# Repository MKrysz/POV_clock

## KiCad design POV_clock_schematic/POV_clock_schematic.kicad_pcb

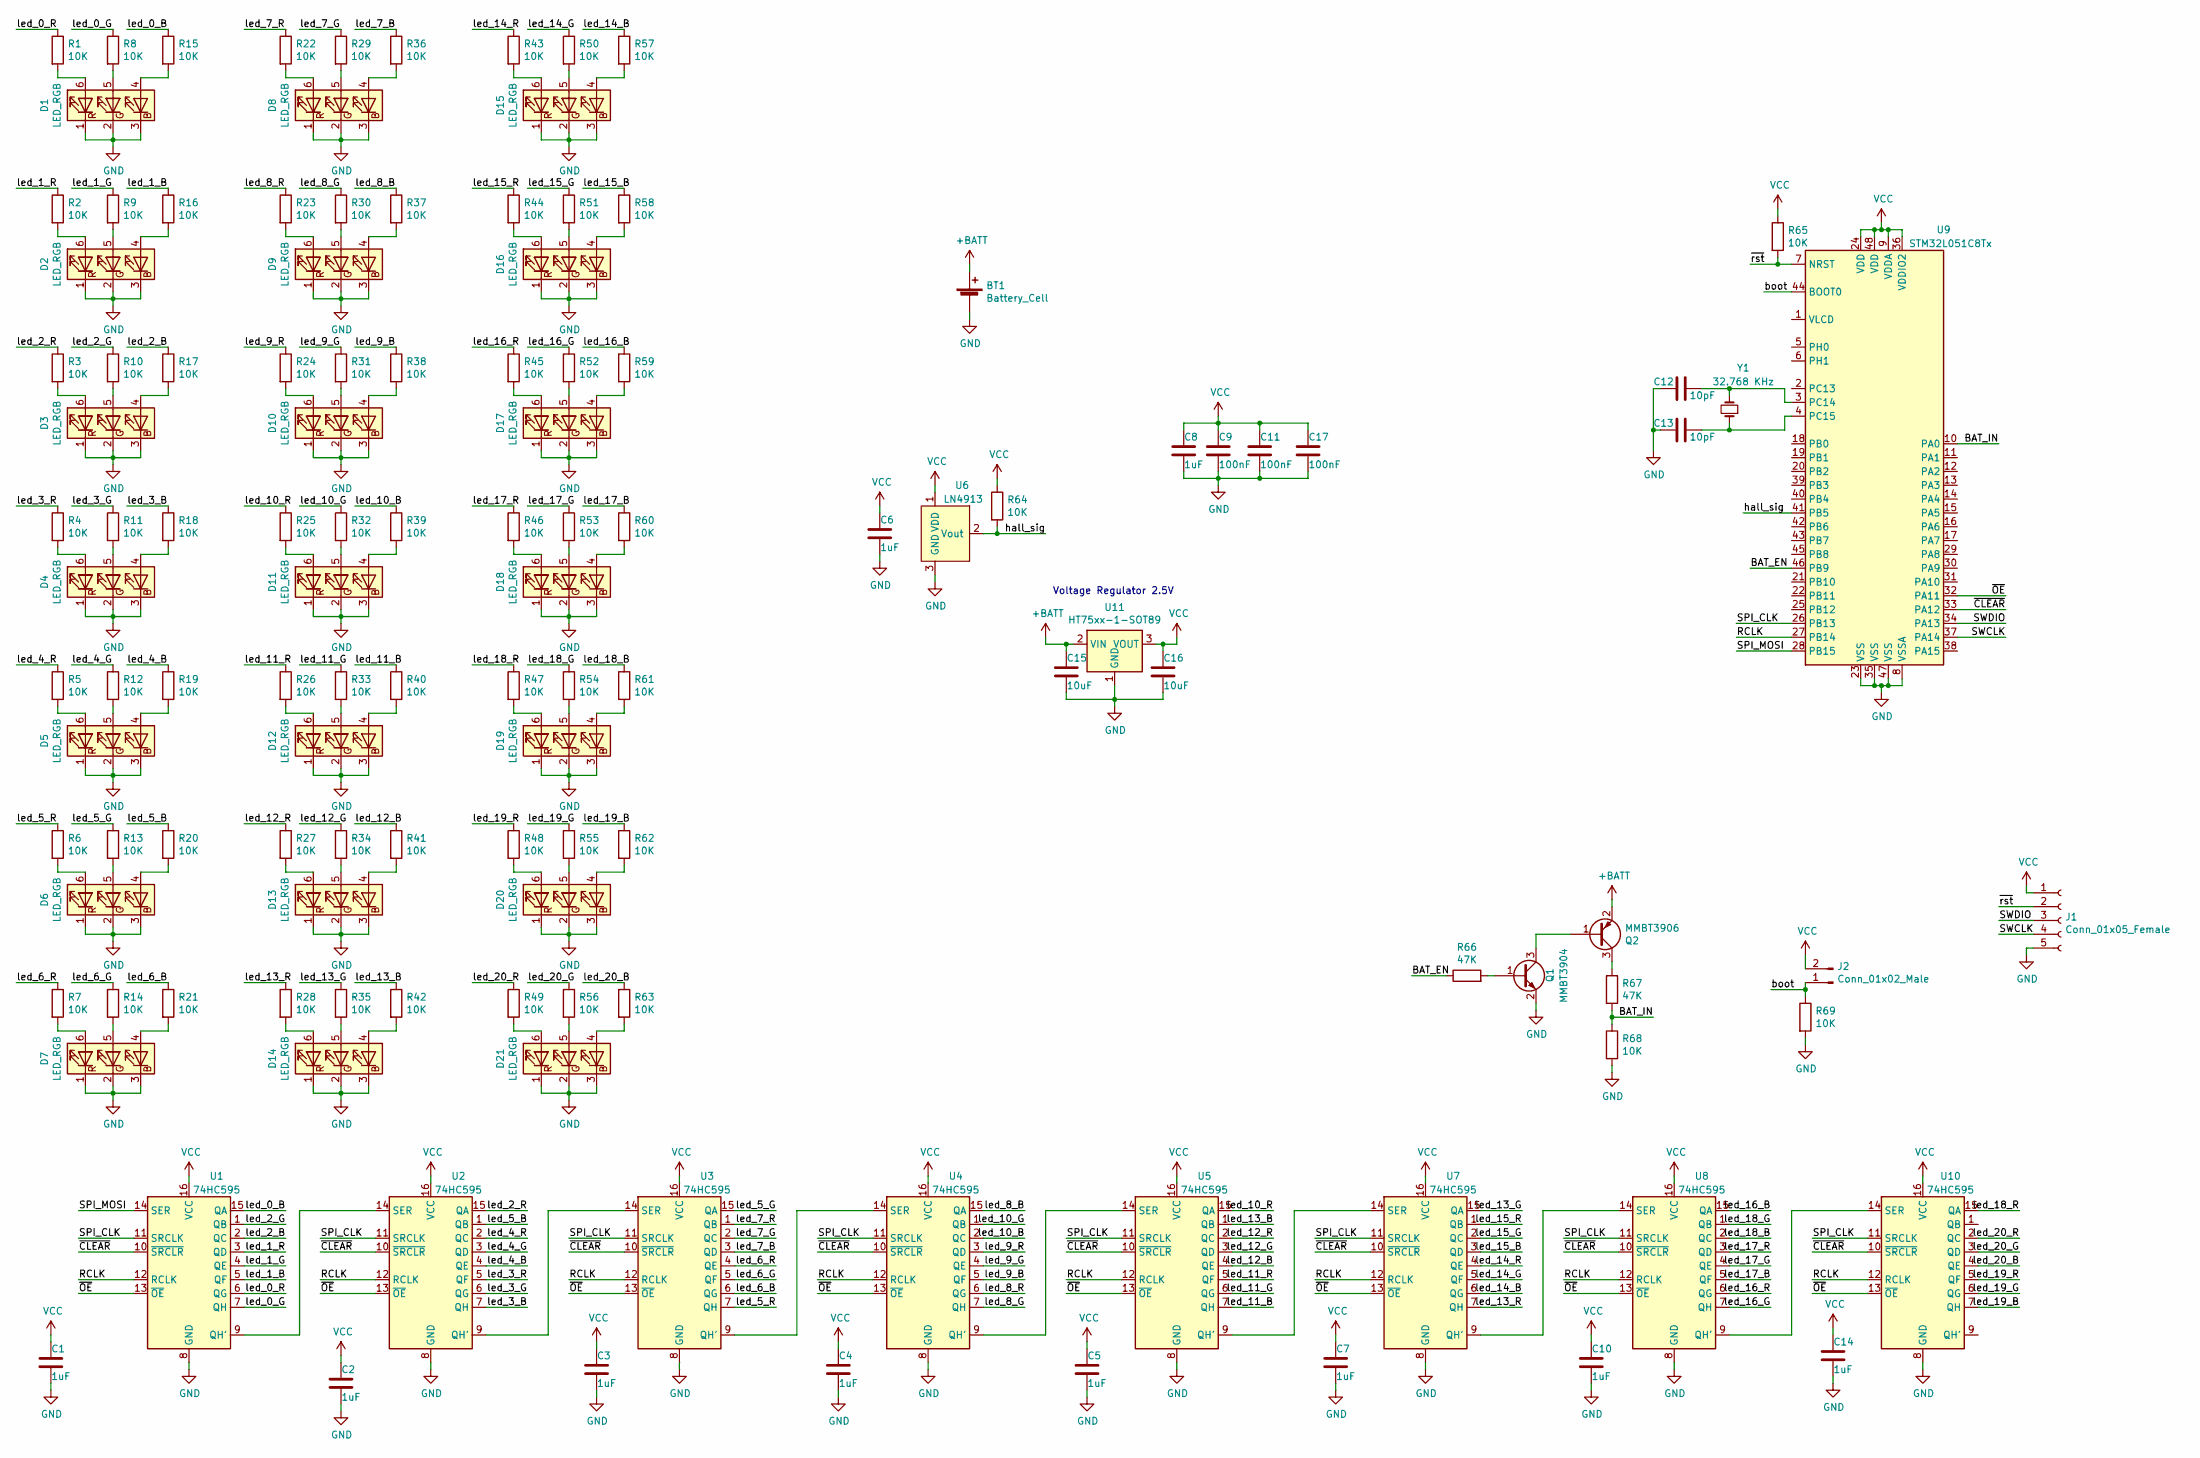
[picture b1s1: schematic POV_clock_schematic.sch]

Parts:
BT1: Battery_Cell; PinHeader_1x02_P2.54mm_Vertical
C1, C2, C3, C4, C5, C6, C7, C8, C10, C14: 1uF; C_1206_3216Metric_Pad1.33x1.80mm_HandSolder
C9, C11, C17: 100nF; C_1206_3216Metric_Pad1.33x1.80mm_HandSolder
C12, C13: 10pF; C_0603_1608Metric_Pad1.08x0.95mm_HandSolder
C15, C16: 10uF; C_1206_3216Metric_Pad1.33x1.80mm_HandSolder
D1, D2, D3, D4, D5, D6, D7, D8, D9, D10, D11, D12, D13, D14, D15, D16, D17, D18, D19, D20, D21: LED_RGB; LED_RGB_5050-6
J1: Conn_01x05_Female; PinHeader_1x05_P2.54mm_Vertical
J2: Conn_01x02_Male; PinHeader_1x02_P2.54mm_Vertical
Q1: MMBT3904; TSOT-23_HandSoldering
Q2: MMBT3906; TSOT-23_HandSoldering
R1, R2, R3, R4, R5, R6, R7, R8, R9, R10, R11, R12, R13, R14, R15, R16, R17, R18, R19, R20, R21, R22, R23, R24, R25, R26, R27, R28, R29, R30, R31, R32, R33, R34, R35, R36, R37, R38, R39, R40, R41, R42, R43, R44, R45, R46, R47, R48, R49, R50, R51, R52, R53, R54, R55, R56, R57, R58, R59, R60, R61, R62, R63, R64, R65: 10K; R_0603_1608Metric_Pad0.98x0.95mm_HandSolder
R66, R67: 47K; R_1206_3216Metric_Pad1.30x1.75mm_HandSolder
R68, R69: 10K; R_1206_3216Metric_Pad1.30x1.75mm_HandSolder
U1, U2, U3, U4, U5, U7, U8, U10: 74HC595; SO-16_3.9x9.9mm_P1.27mm
U6: LN4913; TSOT-23_HandSoldering
U9: STM32L051C8Tx; LQFP-48_7x7mm_P0.5mm
U11: HT75xx-1-SOT89; SOT-89-3_Handsoldering
Y1: 32.768 KHz; Crystal_SMD_2012-2Pin_2.0x1.2mm_HandSoldering

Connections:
+BATT: BT1.1 (+), C15.1, Q2.2 (E), U11.2 (VIN)
/BAT_EN: R66.1, U9.46 (PB9)
/BAT_IN: R67.2, R68.1, U9.10 (PA0)
/RCLK: U1.12 (RCLK), U2.12 (RCLK), U3.12 (RCLK), U4.12 (RCLK), U5.12 (RCLK), U7.12 (RCLK), U8.12 (RCLK), U9.27 (PB14), U10.12 (RCLK)
/SPI_CLK: U1.11 (SRCLK), U2.11 (SRCLK), U3.11 (SRCLK), U4.11 (SRCLK), U5.11 (SRCLK), U7.11 (SRCLK), U8.11 (SRCLK), U9.26 (PB13), U10.11 (SRCLK)
/SPI_MOSI: U1.14 (SER), U9.28 (PB15)
/SWCLK: J1.4, U9.37 (PA14)
/SWDIO: J1.3, U9.34 (PA13)
/boot: J2.1, R69.1, U9.44 (BOOT0)
/hall_sig: R64.2, U6.2 (Vout), U9.41 (PB5)
/led_0_B: R15.1, U1.15 (QA)
/led_0_G: R8.1, U1.7 (QH)
/led_0_R: R1.1, U1.6 (QG)
/led_1_B: R16.1, U1.5 (QF)
/led_1_G: R9.1, U1.4 (QE)
/led_1_R: R2.1, U1.3 (QD)
/led_2_B: R17.1, U1.2 (QC)
/led_2_G: R10.1, U1.1 (QB)
/led_2_R: R3.1, U2.15 (QA)
/led_3_B: R18.1, U2.7 (QH)
/led_3_G: R11.1, U2.6 (QG)
/led_3_R: R4.1, U2.5 (QF)
/led_4_B: R19.1, U2.4 (QE)
/led_4_G: R12.1, U2.3 (QD)
/led_4_R: R5.1, U2.2 (QC)
/led_5_B: R20.1, U2.1 (QB)
/led_5_G: R13.1, U3.15 (QA)
/led_5_R: R6.1, U3.7 (QH)
/led_6_B: R21.1, U3.6 (QG)
/led_6_G: R14.1, U3.5 (QF)
/led_6_R: R7.1, U3.4 (QE)
/led_7_B: R36.1, U3.3 (QD)
/led_7_G: R29.1, U3.2 (QC)
/led_7_R: R22.1, U3.1 (QB)
/led_8_B: R37.1, U4.15 (QA)
/led_8_G: R30.1, U4.7 (QH)
/led_8_R: R23.1, U4.6 (QG)
/led_9_B: R38.1, U4.5 (QF)
/led_9_G: R31.1, U4.4 (QE)
/led_9_R: R24.1, U4.3 (QD)
/led_10_B: R39.1, U4.2 (QC)
/led_10_G: R32.1, U4.1 (QB)
/led_10_R: R25.1, U5.15 (QA)
/led_11_B: R40.1, U5.7 (QH)
/led_11_G: R33.1, U5.6 (QG)
/led_11_R: R26.1, U5.5 (QF)
/led_12_B: R41.1, U5.4 (QE)
/led_12_G: R34.1, U5.3 (QD)
/led_12_R: R27.1, U5.2 (QC)
/led_13_B: R42.1, U5.1 (QB)
/led_13_G: R35.1, U7.15 (QA)
/led_13_R: R28.1, U7.7 (QH)
/led_14_B: R57.1, U7.6 (QG)
/led_14_G: R50.1, U7.5 (QF)
/led_14_R: R43.1, U7.4 (QE)
/led_15_B: R58.1, U7.3 (QD)
/led_15_G: R51.1, U7.2 (QC)
/led_15_R: R44.1, U7.1 (QB)
/led_16_B: R59.1, U8.15 (QA)
/led_16_G: R52.1, U8.7 (QH)
/led_16_R: R45.1, U8.6 (QG)
/led_17_B: R60.1, U8.5 (QF)
/led_17_G: R53.1, U8.4 (QE)
/led_17_R: R46.1, U8.3 (QD)
/led_18_B: R61.1, U8.2 (QC)
/led_18_G: R54.1, U8.1 (QB)
/led_18_R: R47.1, U10.15 (QA)
/led_19_B: R62.1, U10.7 (QH)
/led_19_G: R55.1, U10.6 (QG)
/led_19_R: R48.1, U10.5 (QF)
/led_20_B: R63.1, U10.4 (QE)
/led_20_G: R56.1, U10.3 (QD)
/led_20_R: R49.1, U10.2 (QC)
/~CLEAR: U1.10 (~SRCLR), U2.10 (~SRCLR), U3.10 (~SRCLR), U4.10 (~SRCLR), U5.10 (~SRCLR), U7.10 (~SRCLR), U8.10 (~SRCLR), U9.33 (PA12), U10.10 (~SRCLR)
/~OE: U1.13 (~OE), U2.13 (~OE), U3.13 (~OE), U4.13 (~OE), U5.13 (~OE), U7.13 (~OE), U8.13 (~OE), U9.32 (PA11), U10.13 (~OE)
/~rst: J1.2, R65.2, U9.7 (NRST)
GND: BT1.2 (-), C1.2, C2.2, C3.2, C4.2, C5.2, C6.2, C7.2, C8.2, C9.2, C10.2, C11.2, C12.1, C13.1, C14.2, C15.2, C16.2, C17.2, D1.1 (RK), D1.2 (GK), D1.3 (BK), D2.1 (RK), D2.2 (GK), D2.3 (BK), D3.1 (RK), D3.2 (GK), D3.3 (BK), D4.1 (RK), D4.2 (GK), D4.3 (BK), D5.1 (RK), D5.2 (GK), D5.3 (BK), D6.1 (RK), D6.2 (GK), D6.3 (BK), D7.1 (RK), D7.2 (GK), D7.3 (BK), D8.1 (RK), D8.2 (GK), D8.3 (BK), D9.1 (RK), D9.2 (GK), D9.3 (BK), D10.1 (RK), D10.2 (GK), D10.3 (BK), D11.1 (RK), D11.2 (GK), D11.3 (BK), D12.1 (RK), D12.2 (GK), D12.3 (BK), D13.1 (RK), D13.2 (GK), D13.3 (BK), D14.1 (RK), D14.2 (GK), D14.3 (BK), D15.1 (RK), D15.2 (GK), D15.3 (BK), D16.1 (RK), D16.2 (GK), D16.3 (BK), D17.1 (RK), D17.2 (GK), D17.3 (BK), D18.1 (RK), D18.2 (GK), D18.3 (BK), D19.1 (RK), D19.2 (GK), D19.3 (BK), D20.1 (RK), D20.2 (GK), D20.3 (BK), D21.1 (RK), D21.2 (GK), D21.3 (BK), J1.5, Q1.2 (E), R68.2, R69.2, U1.8 (GND), U2.8 (GND), U3.8 (GND), U4.8 (GND), U5.8 (GND), U6.3 (GND), U7.8 (GND), U8.8 (GND), U9.8 (VSSA), U9.23 (VSS), U9.35 (VSS), U9.47 (VSS), U10.8 (GND), U11.1 (GND)
unnamed: C12.2, U9.3 (PC14), Y1.2
unnamed: C13.2, U9.4 (PC15), Y1.1
unnamed: D1.4 (BA), R15.2
unnamed: D1.5 (GA), R8.2
unnamed: D1.6 (RA), R1.2
unnamed: D2.4 (BA), R16.2
unnamed: D2.5 (GA), R9.2
unnamed: D2.6 (RA), R2.2
unnamed: D3.4 (BA), R17.2
unnamed: D3.5 (GA), R10.2
unnamed: D3.6 (RA), R3.2
unnamed: D4.4 (BA), R18.2
unnamed: D4.5 (GA), R11.2
unnamed: D4.6 (RA), R4.2
unnamed: D5.4 (BA), R19.2
unnamed: D5.5 (GA), R12.2
unnamed: D5.6 (RA), R5.2
unnamed: D6.4 (BA), R20.2
unnamed: D6.5 (GA), R13.2
unnamed: D6.6 (RA), R6.2
unnamed: D7.4 (BA), R21.2
unnamed: D7.5 (GA), R14.2
unnamed: D7.6 (RA), R7.2
unnamed: D8.4 (BA), R36.2
unnamed: D8.5 (GA), R29.2
unnamed: D8.6 (RA), R22.2
unnamed: D9.4 (BA), R37.2
unnamed: D9.5 (GA), R30.2
unnamed: D9.6 (RA), R23.2
unnamed: D10.4 (BA), R38.2
unnamed: D10.5 (GA), R31.2
unnamed: D10.6 (RA), R24.2
unnamed: D11.4 (BA), R39.2
unnamed: D11.5 (GA), R32.2
unnamed: D11.6 (RA), R25.2
unnamed: D12.4 (BA), R40.2
unnamed: D12.5 (GA), R33.2
unnamed: D12.6 (RA), R26.2
unnamed: D13.4 (BA), R41.2
unnamed: D13.5 (GA), R34.2
unnamed: D13.6 (RA), R27.2
unnamed: D14.4 (BA), R42.2
unnamed: D14.5 (GA), R35.2
unnamed: D14.6 (RA), R28.2
unnamed: D15.4 (BA), R57.2
unnamed: D15.5 (GA), R50.2
unnamed: D15.6 (RA), R43.2
unnamed: D16.4 (BA), R58.2
unnamed: D16.5 (GA), R51.2
unnamed: D16.6 (RA), R44.2
unnamed: D17.4 (BA), R59.2
unnamed: D17.5 (GA), R52.2
unnamed: D17.6 (RA), R45.2
unnamed: D18.4 (BA), R60.2
unnamed: D18.5 (GA), R53.2
unnamed: D18.6 (RA), R46.2
unnamed: D19.4 (BA), R61.2
unnamed: D19.5 (GA), R54.2
unnamed: D19.6 (RA), R47.2
unnamed: D20.4 (BA), R62.2
unnamed: D20.5 (GA), R55.2
unnamed: D20.6 (RA), R48.2
unnamed: D21.4 (BA), R63.2
unnamed: D21.5 (GA), R56.2
unnamed: D21.6 (RA), R49.2
unnamed: Q1.1 (B), R66.2
unnamed: Q1.3 (C), Q2.1 (B)
unnamed: Q2.3 (C), R67.1
unnamed: U1.9 (QH'), U2.14 (SER)
unnamed: U2.9 (QH'), U3.14 (SER)
unnamed: U3.9 (QH'), U4.14 (SER)
unnamed: U4.9 (QH'), U5.14 (SER)
unnamed: U5.9 (QH'), U7.14 (SER)
unnamed: U7.9 (QH'), U8.14 (SER)
unnamed: U8.9 (QH'), U10.14 (SER)
VCC: C1.1, C2.1, C3.1, C4.1, C5.1, C6.1, C7.1, C8.1, C9.1, C10.1, C11.1, C14.1, C16.1, C17.1, J1.1, J2.2, R64.1, R65.1, U1.16 (VCC), U2.16 (VCC), U3.16 (VCC), U4.16 (VCC), U5.16 (VCC), U6.1 (VDD), U7.16 (VCC), U8.16 (VCC), U9.9 (VDDA), U9.24 (VDD), U9.36 (VDDIO2), U9.48 (VDD), U10.16 (VCC), U11.3 (VOUT)

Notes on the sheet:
Voltage Regulator 2.5V

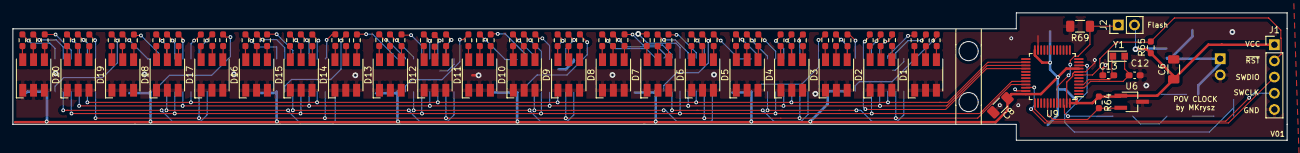
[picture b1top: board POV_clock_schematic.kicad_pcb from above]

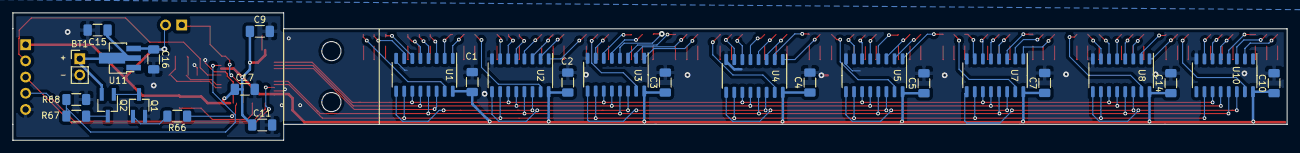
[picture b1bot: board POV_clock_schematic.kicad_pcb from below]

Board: 2 copper layers, 200.0 x 20.0 mm, 124 parts (28 on the bottom side), 153 nets.

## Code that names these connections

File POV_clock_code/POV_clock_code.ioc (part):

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Mcu.Name=STM32L051C(6-8)Tx
Mcu.Package=LQFP48
Mcu.UserName=STM32L051C8Tx
PA0.Mode=IN0
PA0.Signal=ADC_IN0
PA11.GPIOParameters=GPIO_Label
PA11.GPIO_Label=NOT_OE
PA11.Signal=GPIO_Output
PA12.GPIOParameters=GPIO_Label
PA12.GPIO_Label=NOT_CLEAR
PA12.Signal=GPIO_Output
PA13.Mode=Serial_Wire
PA13.Signal=SYS_SWDIO
PA14.Mode=Serial_Wire
PA14.Signal=SYS_SWCLK
PB13.Mode=TX_Only_Simplex_Unidirect_Master
PB13.Signal=SPI2_SCK
PB14.GPIOParameters=GPIO_Label
PB14.GPIO_Label=RCLK
PB14.Signal=GPIO_Output
PB15.Mode=TX_Only_Simplex_Unidirect_Master
PB15.Signal=SPI2_MOSI
PB5.GPIOParameters=GPIO_Label
PB5.GPIO_Label=hal_sig
PB5.Signal=GPXTI5
PB9.Signal=GPIO_Output
PC14-OSC32_IN.Mode=LSE-External-Oscillator
PC14-OSC32_IN.Signal=RCC_OSC32_IN
PC15-OSC32_OUT.Mode=LSE-External-Oscillator
PC15-OSC32_OUT.Signal=RCC_OSC32_OUT
RCC.HSE_VALUE=8000000
RCC.SYSCLKFreq_VALUE=2097000
board=custom

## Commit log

2021-12-04 Hardware version v01
